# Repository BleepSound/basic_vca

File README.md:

[![CC BY-SA 4.0][cc-by-sa-shield]][cc-by-sa]

# Quad VCA

Latest documentation available at https://bleepsound.github.io/modules/

[![CC BY-SA 4.0][cc-by-sa-image]][cc-by-sa]

[cc-by-sa]: http://creativecommons.org/licenses/by-sa/4.0/
[cc-by-sa-image]: https://licensebuttons.net/l/by-sa/4.0/88x31.png
[cc-by-sa-shield]: https://img.shields.io/badge/License-CC%20BY--SA%204.0-lightgrey.svg

[![CC BY-SA 4.0][cc-by-sa-shield]][cc-by-sa]

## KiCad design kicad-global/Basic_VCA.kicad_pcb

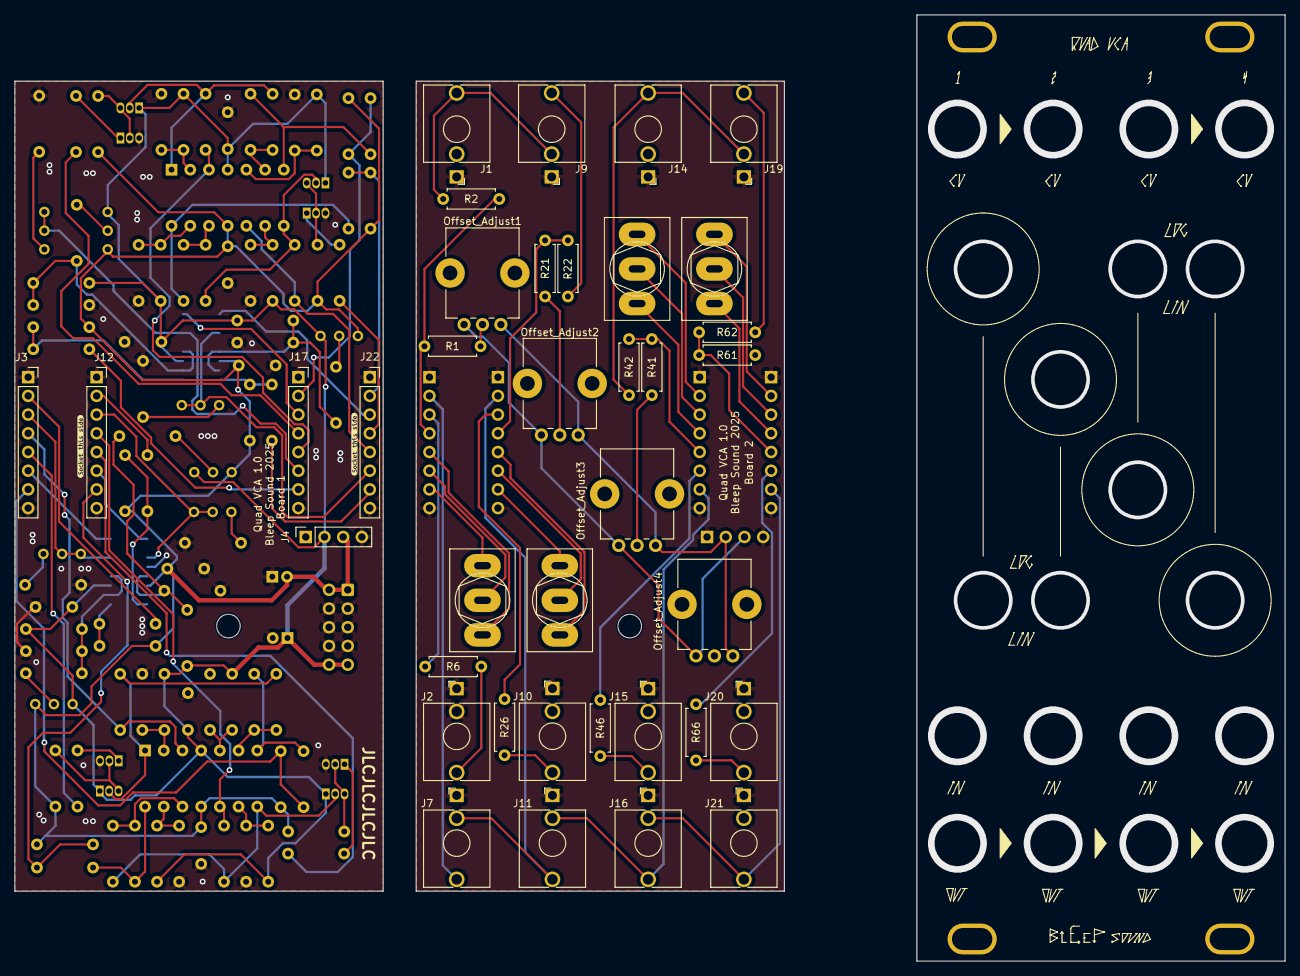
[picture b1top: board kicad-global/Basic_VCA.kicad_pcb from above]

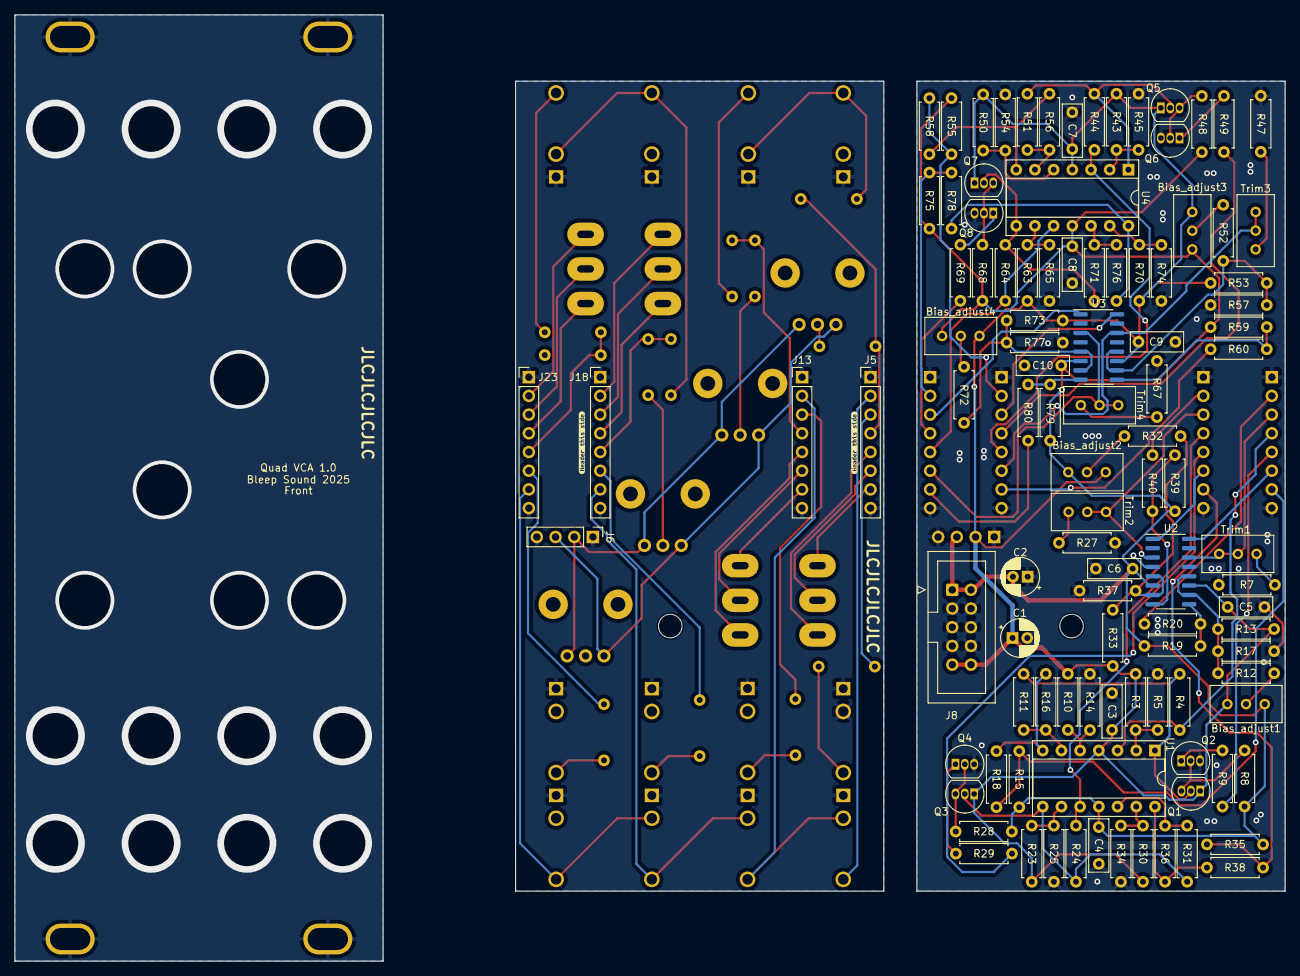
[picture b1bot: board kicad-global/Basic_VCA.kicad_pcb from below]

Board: 2 copper layers, 172.5 x 128.5 mm, 151 parts (106 on the bottom side), 83 nets.

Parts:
Bias_adjust1, Bias_adjust2, Bias_adjust3, Bias_adjust4: 100k; Potentiometer_Bourns_3296W_Vertical
C1, C2: 10uF; CP_Radial_D5.0mm_P2.00mm
C3, C4, C5, C6, C7, C8, C9, C10: 100nF; C_Disc_D7.0mm_W2.5mm_P5.00mm
H1, H2: SpacerHoles; MountingHole_3.2mm_M3
H3, H4, H5, H6: MountingHole_Pad; Doepfer Mounting hole
J1, J9, J14, J19: CV; Thonkiconn
J2, J10, J15, J20: In; Thonkiconn
J3, J12, J17, J22: Conn_Circuit; PinSocket_1x08_P2.54mm_Vertical
J4: Conn_power; PinSocket_1x04_P2.54mm_Vertical
J5, J13, J18, J23: Conn_Jack; PinHeader_1x08_P2.54mm_Vertical
J6: Conn_power; PinHeader_1x04_P2.54mm_Vertical
J7, J11, J16, J21: Out; Thonkiconn
J8: Power Input; IDC-Header_2x05_P2.54mm_Vertical
Offset_Adjust1, Offset_Adjust2, Offset_Adjust3, Offset_Adjust4: 100k; Pot-bourns-alpha
Q1, Q3, Q5, Q7: 2N3904; TO-92_Inline
Q2, Q4, Q6, Q8: 2N3906; TO-92_Inline
R1, R2, R3, R6, R10, R16, R21, R22, R23, R26, R30, R36, R41, R42, R43, R46, R50, R56, R61, R62, R63, R66, R70, R76: 100k; R_Axial_DIN0207_L6.3mm_D2.5mm_P7.62mm_Horizontal
R4, R5, R11, R24, R25, R31, R44, R45, R51, R64, R65, R71: 2k; R_Axial_DIN0207_L6.3mm_D2.5mm_P7.62mm_Horizontal
R7, R27, R47, R67: 150R; R_Axial_DIN0207_L6.3mm_D2.5mm_P7.62mm_Horizontal
R8, R28, R48, R68: 120k; R_Axial_DIN0207_L6.3mm_D2.5mm_P7.62mm_Horizontal
R9, R15, R29, R35, R49, R55, R69, R75: 20k; R_Axial_DIN0207_L6.3mm_D2.5mm_P7.62mm_Horizontal
R12, R32, R52, R72: 2M; R_Axial_DIN0207_L6.3mm_D2.5mm_P7.62mm_Horizontal
R13, R33, R53, R73: 470k; R_Axial_DIN0207_L6.3mm_D2.5mm_P7.62mm_Horizontal
R14, R34, R54, R74: 470R; R_Axial_DIN0207_L6.3mm_D2.5mm_P7.62mm_Horizontal
R17, R37, R57, R77: 47k; R_Axial_DIN0207_L6.3mm_D2.5mm_P7.62mm_Horizontal
R18, R38, R58, R78: 30k; R_Axial_DIN0207_L6.3mm_D2.5mm_P7.62mm_Horizontal
R19, R39, R59, R79: 4.7k; R_Axial_DIN0207_L6.3mm_D2.5mm_P7.62mm_Horizontal
R20, R40, R60, R80: 1k; R_Axial_DIN0207_L6.3mm_D2.5mm_P7.62mm_Horizontal
SW1, SW2, SW3, SW4: log/lin; SW_Toggle_Blue_wSlots
Trim1, Trim2, Trim3, Trim4: 2k; Potentiometer_Bourns_3296W_Vertical
U1, U4: TL074; DIP-14_W7.62mm_Socket
U2, U3: LM13700; SOIC-16_3.9x9.9mm_P1.27mm
kibuzzard-67840646, kibuzzard-67840646#2: G***; kibuzzard-67840646
kibuzzard-67840666, kibuzzard-67840666#2: G***; kibuzzard-67840666

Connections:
+12V: Bias_adjust1.1, Bias_adjust2.1, Bias_adjust3.1, Bias_adjust4.1, C1.1, C3.1, C5.1, C7.1, C9.1, J4.2, J6.2, J8.9, J8.10, Offset_Adjust1.3, Offset_Adjust2.3, Offset_Adjust3.3, Offset_Adjust4.3, Q1.1 (C), Q3.1 (C), Q5.1 (C), Q7.1 (C), R3.2, R10.2, R13.2, R23.2, R30.2, R33.2, R43.2, R50.2, R53.2, R63.2, R70.2, R73.2, U1.4 (V+), U2.11 (V+), U3.11 (V+), U4.4 (V+)
-12V: Bias_adjust1.3, Bias_adjust2.3, Bias_adjust3.3, Bias_adjust4.3, C2.2, C4.2, C6.2, C8.2, C10.2, J4.3, J6.3, J8.1, J8.2, Offset_Adjust1.1, Offset_Adjust2.1, Offset_Adjust3.1, Offset_Adjust4.1, R8.2, R15.2, R19.2, R28.2, R35.2, R39.2, R48.2, R55.2, R59.2, R68.2, R75.2, R79.2, U1.11 (V-), U2.6 (V-), U3.6 (V-), U4.11 (V-)
/Amp_bias1: J3.6, J5.6, SW1.2 (B), U2.16
/In1: J3.3, J5.3, R6.1, Trim1.1, Trim1.2, U2.14 (+)
/Offset1: J3.4, J5.4, R1.1, R2.1, R4.2, U1.3 (+)
/Out1: J3.2, J5.2, J7.T, R20.1
/VCA_2/Amp_bias2: J12.6, J13.6, SW2.2 (B), U2.1
/VCA_2/In2: J12.3, J13.3, R26.1, Trim2.1, Trim2.2, U2.3 (+)
/VCA_2/Offset2: J12.4, J13.4, R21.1, R22.1, R24.2, U1.10 (+)
/VCA_2/lin2: J12.7, J13.7, R35.1, R38.2, SW2.3 (C)
/VCA_2/log2: J12.5, J13.5, R29.2, SW2.1 (A)
/VCA_3/Amp_bias3: J17.3, J18.3, SW3.2 (B), U3.16
/VCA_3/In3: J17.6, J18.6, R46.1, Trim3.1, Trim3.2, U3.14 (+)
/VCA_3/Offset3: J17.5, J18.5, R41.1, R42.1, R44.2, U4.3 (+)
/VCA_3/lin3: J17.2, J18.2, R55.1, R58.2, SW3.3 (C)
/VCA_3/log3: J17.4, J18.4, R49.2, SW3.1 (A)
/VCA_4/Amp_bias4: J22.3, J23.3, SW4.2 (B), U3.1
/VCA_4/In4: J22.6, J23.6, R66.1, Trim4.1, Trim4.2, U3.3 (+)
/VCA_4/Offset4: J22.5, J23.5, R61.1, R62.1, R64.2, U4.10 (+)
/VCA_4/lin4: J22.2, J23.2, R75.1, R78.2, SW4.3 (C)
/VCA_4/log4: J22.4, J23.4, R69.2, SW4.1 (A)
/lin1: J3.7, J5.7, R15.1, R18.2, SW1.3 (C)
/log1: J3.5, J5.5, R9.2, SW1.1 (A)
CV1: J1.T, J9.TN, R2.2
CV3: J14.T, J19.TN, R42.2
GND: C1.2, C2.1, C3.2, C4.1, C5.2, C6.1, C7.2, C8.1, C9.2, C10.1, H3.1, H4.1, H5.1, H6.1, J1.S, J2.S, J2.TN, J3.1, J3.8, J4.1, J4.4, J5.1, J5.8, J6.1, J6.4, J7.S, J8.3, J8.4, J8.5, J8.6, J8.7, J8.8, J9.S, J10.S, J11.S, J12.1, J12.8, J13.1, J13.8, J14.S, J15.S, J16.S, J17.1, J17.8, J18.1, J18.8, J19.S, J20.S, J21.S, J22.1, J22.8, J23.1, J23.8, Q2.3 (E), Q4.3 (E), Q6.3 (E), Q8.3 (E), R5.1, R7.2, R14.1, R17.1, R25.1, R27.2, R34.1, R37.1, R45.1, R47.2, R54.1, R57.1, R65.1, R67.2, R74.1, R77.1, U2.4 (-), U2.13 (-), U3.4 (-), U3.13 (-)
unnamed: Bias_adjust1.2, R12.2
unnamed: Bias_adjust2.2, R32.2
unnamed: Bias_adjust3.2, R52.2
unnamed: Bias_adjust4.2, R72.2
unnamed: J2.T, R6.2
unnamed: J9.T, R22.2
unnamed: J10.T, R26.2
unnamed: J15.T, R46.2
unnamed: J19.T, R62.2
unnamed: J20.T, R66.2
unnamed: Offset_Adjust1.2, R1.2
unnamed: Offset_Adjust2.2, R21.2
unnamed: Offset_Adjust3.2, R41.2
unnamed: Offset_Adjust4.2, R61.2
unnamed: Q1.2 (B), R4.1, R11.2, U1.1
unnamed: Q1.3 (E), Q2.2 (B), R8.1
unnamed: Q2.1 (C), R9.1
unnamed: Q3.2 (B), R24.1, R31.2, U1.8
unnamed: Q3.3 (E), Q4.2 (B), R28.1
unnamed: Q4.1 (C), R29.1
unnamed: Q5.2 (B), R44.1, R51.2, U4.1
unnamed: Q5.3 (E), Q6.2 (B), R48.1
unnamed: Q6.1 (C), R49.1
unnamed: Q7.2 (B), R64.1, R71.2, U4.8
unnamed: Q7.3 (E), Q8.2 (B), R68.1
unnamed: Q8.1 (C), R69.1
unnamed: R7.1, Trim1.3
unnamed: R12.1, R13.1, R17.2, U2.10, U2.12
unnamed: R16.1, R18.1, U1.7
unnamed: R19.1, R20.2, U2.9
unnamed: R27.1, Trim2.3
unnamed: R32.1, R33.1, R37.2, U2.5, U2.7
unnamed: R36.1, R38.1, U1.14
unnamed: R39.1, R40.2, U2.8
unnamed: R47.1, Trim3.3
unnamed: R52.1, R53.1, R57.2, U3.10, U3.12
unnamed: R56.1, R58.1, U4.7
unnamed: R59.1, R60.2, U3.9
unnamed: R67.1, Trim4.3
unnamed: R72.1, R73.1, R77.2, U3.5, U3.7
unnamed: R76.1, R78.1, U4.14
unnamed: R79.1, R80.2, U3.8
unnamed: R3.1, R5.2, U1.2 (-)
unnamed: R10.1, R14.2, U1.5 (+)
unnamed: R11.1, R16.2, U1.6 (-)
unnamed: R23.1, R25.2, U1.9 (-)
unnamed: R31.1, R36.2, U1.12 (+)
unnamed: R30.1, R34.2, U1.13 (-)
unnamed: R43.1, R45.2, U4.2 (-)
unnamed: R50.1, R54.2, U4.5 (+)
unnamed: R51.1, R56.2, U4.6 (-)
unnamed: R63.1, R65.2, U4.9 (-)
unnamed: R71.1, R76.2, U4.12 (+)
unnamed: R70.1, R74.2, U4.13 (-)
Out2: J7.TN, J11.T, J12.2, J13.2, R40.1
Out3: J11.TN, J16.T, J17.7, J18.7, R60.1
Out4: J16.TN, J21.T, J22.7, J23.7, R80.1

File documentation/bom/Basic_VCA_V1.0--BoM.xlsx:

Basic_VCA_V1.0 Bill of Materials
Schematic: | Basic_VCA | Component Groups: | 30
Variant: | default | Component Count: | 141 (0 SMD/ 137 THT)
Revision: | 1.0 | Fitted Components: | 141 (0 SMD/ 137 THT)
Date: | 2025-01-13 | Number of PCBs: | 1
KiCad Version: | 8.0.6-8.0.6-0~ubuntu22.04.1 | Total Components: | 141
Row | Description | References | Value | Quantity Per PCB | Links
1 | Trimmer potentiometer, 25 turn series 3296W | Bias_adjust1 Bias_adjust2 Bias_adjust3 Bias_adjust4 | 100k | 4 | https://www.thonk.co.uk/shop/25-turn-trimmer-potentiometer/
2 | Ceramic disc capacitor 50V 20% | C3 C4 C5 C6 C7 C8 C9 C10 | 100nF | 8 | https://www.taydaelectronics.com/capacitors/ceramic-disc-cap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
3 | 10uF Electrolytic capacitor, 2.0mm pitch, 5mm diameter | C1 C2 | 10uF | 2 | https://www.taydaelectronics.com/capacitors/electrolytic-cap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
4 | Thonkiconn jack | J1 J9 J14 J19 | CV | 4 | https://www.thonk.co.uk/shop/thonkiconn/
5 | 2.54mm pitch pin socket vertical 1x8pos | J3 J12 J17 J22 | Conn_Circuit | 4
6 | 2.54mm pitch pin header vertical 1x8pos | J5 J13 J18 J23 | Conn_Jack | 4
7 | 2.54mm pitch pin socket vertical 1x4pos | J4 | Conn_power | 1
8 | 2.54mm pitch pin header vertical 1x4pos | J6 | Conn_power | 1
9 | Thonkiconn jack | J2 J10 J15 J20 | In | 4 | https://www.thonk.co.uk/shop/thonkiconn/
10 | Thonkiconn jack | J7 J11 J16 J21 | Out | 4 | https://www.thonk.co.uk/shop/thonkiconn/
11 | Eurorack 10 pin shrouded power header IDC | J8 | Power Input | 1 | https://www.thonk.co.uk/shop/eurorack-diy-essentials/
12 | Alpha/bourns vertical potentiometer | Offset_Adjust1 Offset_Adjust2 Offset_Adjust3 Offset_Adjust4 | 100k | 4 | https://www.thonk.co.uk/shop/alpha-9mm-pots/
13 | 2N3904 NPN General Purpose Transistor | Q1 Q3 Q5 Q7 | 2N3904 | 4 | https://www.taydaelectronics.com/2n3904-npn-general-propose-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
14 | 2N3906 PNP General Purpose Transistor | Q2 Q4 Q6 Q8 | 2N3906 | 4 | https://www.taydaelectronics.com/2n3906-general-propose-pnp-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
15 | 2.5mm*6.8mm 1/4W 1% Metal film resistor | R7 R27 R47 R67 | 150R | 4 | https://www.taydaelectronics.com/resistors/1-4w-metal-film-r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
16 | 2.5mm*6.8mm 1/4W 1% Metal film resistor | R14 R34 R54 R74 | 470R | 4 | https://www.taydaelectronics.com/resistors/1-4w-metal-film-r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
17 | 2.5mm*6.8mm 1/4W 1% Metal film resistor | R20 R40 R60 R80 | 1k | 4 | https://www.taydaelectronics.com/resistors/1-4w-metal-film-r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
18 | 2.5mm*6.8mm 1/4W 1% Metal film resistor | R4 R5 R11 R24 R25 R31 R44 R45 R51 R64 R65 R71 | 2k | 12 | https://www.taydaelectronics.com/resistors/1-4w-metal-film-r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
19 | 2.5mm*6.8mm 1/4W 1% Metal film resistor | R19 R39 R59 R79 | 4.7k | 4 | https://www.taydaelectronics.com/resistors/1-4w-metal-film-r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
20 | 2.5mm*6.8mm 1/4W 1% Metal film resistor | R9 R15 R29 R35 R49 R55 R69 R75 | 20k | 8 | https://www.taydaelectronics.com/resistors/1-4w-metal-film-r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
21 | 2.5mm*6.8mm 1/4W 1% Metal film resistor | R18 R38 R58 R78 | 30k | 4 | https://www.taydaelectronics.com/resistors/1-4w-metal-film-r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
22 | 2.5mm*6.8mm 1/4W 1% Metal film resistor | R17 R37 R57 R77 | 47k | 4 | https://www.taydaelectronics.com/resistors/1-4w-metal-film-r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
23 | 2.5mm*6.8mm 1/4W 1% Metal film resistor | R1 R2 R3 R6 R10 R16 R21 R22 R23 R26 R30 R36 R41 R42 R43 R46 R50 R56 R61 R62 R63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 | 100k | 24 | https://www.taydaelectronics.com/resistors/1-4w-metal-film-r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
24 | 2.5mm*6.8mm 1/4W 1% Metal film resistor | R8 R28 R48 R68 | 120k | 4 | https://www.taydaelectronics.com/resistors/1-4w-metal-film-r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
25 | 2.5mm*6.8mm 1/4W 1% Metal film resistor | R13 R33 R53 R73 | 470k | 4 | https://www.taydaelectronics.com/resistors/1-4w-metal-film-r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
26 | 2.5mm*6.8mm 1/4W 1% Metal film resistor | R12 R32 R52 R72 | 2M | 4 | https://www.taydaelectronics.com/resistors/1-4w-metal-film-r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
27 | SPDT ON-ON toggle switch | SW1 SW2 SW3 SW4 | log/lin | 4 | https://www.thonk.co.uk/shop/mini-toggle-switches/
28 | Trimmer potentiometer, 25 turn series 3296W | Trim1 Trim2 Trim3 Trim4 | 2k | 4 | https://www.thonk.co.uk/shop/25-turn-trimmer-potentiometer/
29 | Dual Transconductance Amplifiers | U2 U3 | LM13700 | 2 | https://eu.mouser.com/c/semiconductors/amplifier-ics/transco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
30 | Quad Op-Amp | U1 U4 | TL074 | 2 | https://www.thonk.co.uk/shop/eurorack-diy-essentials/

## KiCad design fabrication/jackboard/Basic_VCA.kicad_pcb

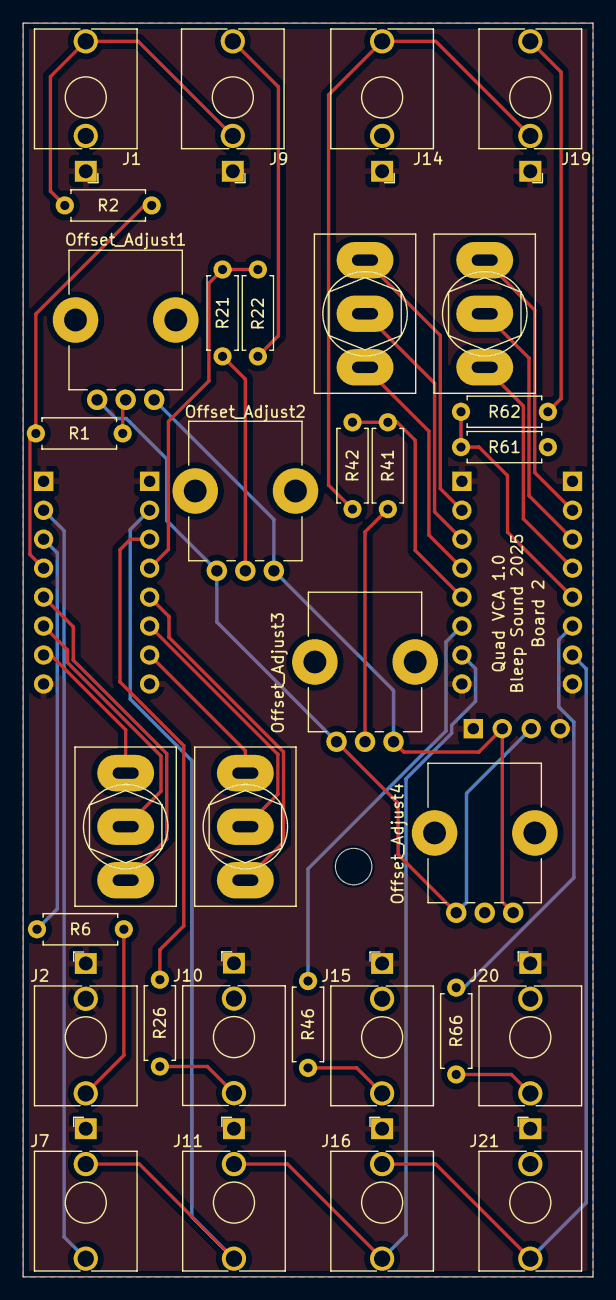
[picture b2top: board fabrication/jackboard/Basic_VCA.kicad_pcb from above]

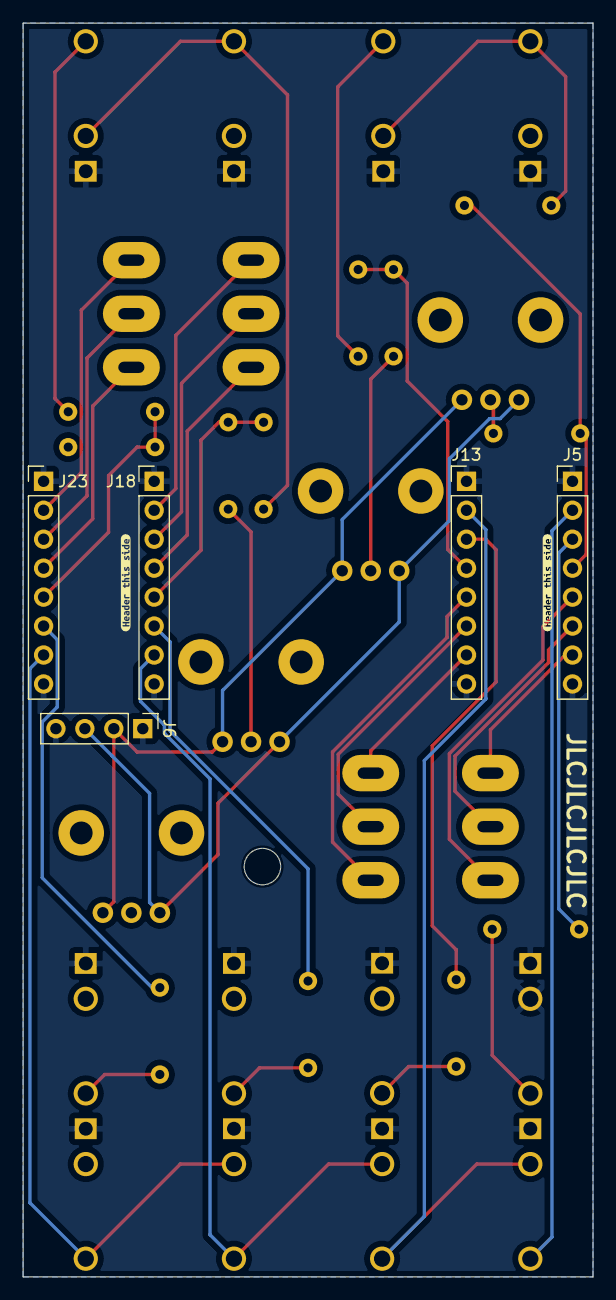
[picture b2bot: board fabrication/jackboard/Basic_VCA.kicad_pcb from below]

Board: 2 copper layers, 50.0 x 110.0 mm, 40 parts (7 on the bottom side), 39 nets.

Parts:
H1: SpacerHoles; MountingHole_3.2mm_M3
J1, J9, J14, J19: CV; Thonkiconn
J2, J10, J15, J20: In; Thonkiconn
J5, J13, J18, J23: Conn_Jack; PinHeader_1x08_P2.54mm_Vertical
J6: Conn_power; PinHeader_1x04_P2.54mm_Vertical
J7, J11, J16, J21: Out; Thonkiconn
Offset_Adjust1, Offset_Adjust2, Offset_Adjust3, Offset_Adjust4: 100k; Pot-bourns-alpha
R1, R2, R6, R21, R22, R26, R41, R42, R46, R61, R62, R66: 100k; R_Axial_DIN0207_L6.3mm_D2.5mm_P7.62mm_Horizontal
SW1, SW2, SW3, SW4: log/lin; SW_Toggle_Blue_wSlots
kibuzzard-67840666, kibuzzard-67840666#2: G***; kibuzzard-67840666

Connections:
+12V: J6.2, Offset_Adjust1.3, Offset_Adjust2.3, Offset_Adjust3.3, Offset_Adjust4.3
-12V: J6.3, Offset_Adjust1.1, Offset_Adjust2.1, Offset_Adjust3.1, Offset_Adjust4.1
/Amp_bias1: J5.6, SW1.2 (B)
/In1: J5.3, R6.1
/Offset1: J5.4, R1.1, R2.1
/Out1: J5.2, J7.T
/VCA_2/Amp_bias2: J13.6, SW2.2 (B)
/VCA_2/In2: J13.3, R26.1
/VCA_2/Offset2: J13.4, R21.1, R22.1
/VCA_2/lin2: J13.7, SW2.3 (C)
/VCA_2/log2: J13.5, SW2.1 (A)
/VCA_3/Amp_bias3: J18.3, SW3.2 (B)
/VCA_3/In3: J18.6, R46.1
/VCA_3/Offset3: J18.5, R41.1, R42.1
/VCA_3/lin3: J18.2, SW3.3 (C)
/VCA_3/log3: J18.4, SW3.1 (A)
/VCA_4/Amp_bias4: J23.3, SW4.2 (B)
/VCA_4/In4: J23.6, R66.1
/VCA_4/Offset4: J23.5, R61.1, R62.1
/VCA_4/lin4: J23.2, SW4.3 (C)
/VCA_4/log4: J23.4, SW4.1 (A)
/lin1: J5.7, SW1.3 (C)
/log1: J5.5, SW1.1 (A)
CV1: J1.T, J9.TN, R2.2
CV3: J14.T, J19.TN, R42.2
GND: J1.S, J2.S, J2.TN, J5.1, J5.8, J6.1, J6.4, J7.S, J9.S, J10.S, J11.S, J13.1, J13.8, J14.S, J15.S, J16.S, J18.1, J18.8, J19.S, J20.S, J21.S, J23.1, J23.8
unnamed: J2.T, R6.2
unnamed: J9.T, R22.2
unnamed: J10.T, R26.2
unnamed: J15.T, R46.2
unnamed: J19.T, R62.2
unnamed: J20.T, R66.2
unnamed: Offset_Adjust1.2, R1.2
unnamed: Offset_Adjust2.2, R21.2
unnamed: Offset_Adjust3.2, R41.2
unnamed: Offset_Adjust4.2, R61.2
Out2: J7.TN, J11.T, J13.2
Out3: J11.TN, J16.T, J18.7
Out4: J16.TN, J21.T, J23.7

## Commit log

2025-01-13 V1.0 finished
2025-01-13 fix issue with silkscreen on front panel
2025-01-15 updated doc
2025-11-27 add licence
